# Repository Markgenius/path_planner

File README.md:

# path_planner
A line following path planner using own made iic light sensor board

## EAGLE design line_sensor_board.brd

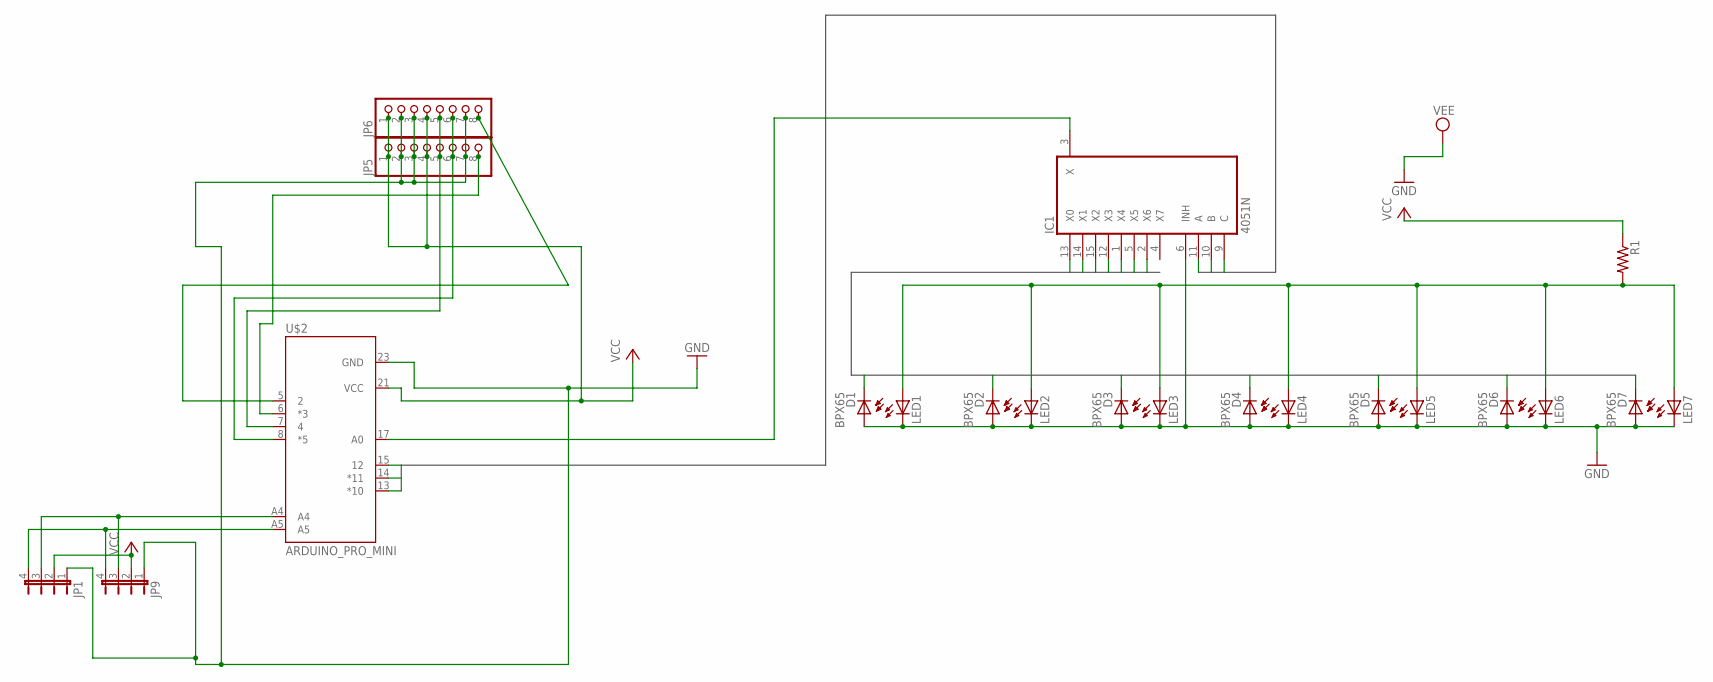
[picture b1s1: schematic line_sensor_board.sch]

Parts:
D1, D2, D3, D4, D5, D6, D7: BPX65
IC1: 4051N; DIL16
JP1, JP9: JP4E; JP4
JP5, JP6: PINHD-1X8; 1X08
LED1, LED2, LED3, LED4, LED5, LED6, LED7: LED3MM
R1: R-US_0204/5; 0204/5
U$2: ARDUINO_PRO_MINI

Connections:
A1: IC1.11 (A), U$2.15 (12)
A2: IC1.10 (B), U$2.14 (*11)
A3: IC1.9 (C), U$2.13 (*10)
B1: D7.K (C), IC1.13 (X0)
B2: D6.K (C), IC1.14 (X1)
B3: D5.K (C), IC1.15 (X2)
B4: D4.K (C), IC1.12 (X3)
B5: D3.K (C), IC1.1 (X4)
B6: D2.K (C), IC1.5 (X5)
B7: D1.K (C), IC1.2 (X6)
GND: D1.A, D2.A, D3.A, D4.A, D5.A, D6.A, D7.A, IC1.6 (INH), IC1.7 (VEE), IC1.8 (GND), JP1.1, JP5.2, JP5.3, JP5.7, JP6.2, JP6.3, JP6.7, JP9.1, LED1.K (C), LED2.K (C), LED3.K (C), LED4.K (C), LED5.K (C), LED6.K (C), LED7.K (C), U$2.23 (GND)
unnamed: IC1.3 (X), U$2.17 (A0)
unnamed: JP1.3, JP9.3, U$2.A4
unnamed: JP1.4, JP9.4, U$2.A5
unnamed: JP5.5, JP6.5, U$2.7 (4)
unnamed: JP5.6, JP6.6, U$2.8 (*5)
unnamed: JP5.8, U$2.6 (*3)
unnamed: LED1.A, LED2.A, LED3.A, LED4.A, LED5.A, LED6.A, LED7.A, R1.2
unnamed: JP6.8, U$2.5 (2)
VCC: IC1.16 (VCC), JP1.2, JP5.1, JP5.4, JP6.1, JP6.4, JP9.2, R1.1, U$2.21 (VCC)

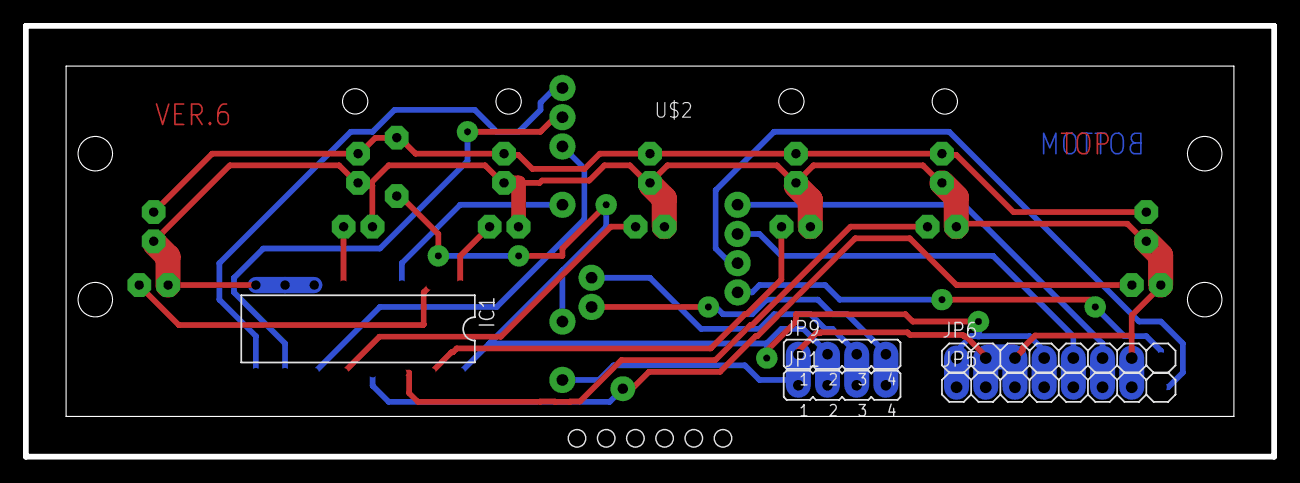
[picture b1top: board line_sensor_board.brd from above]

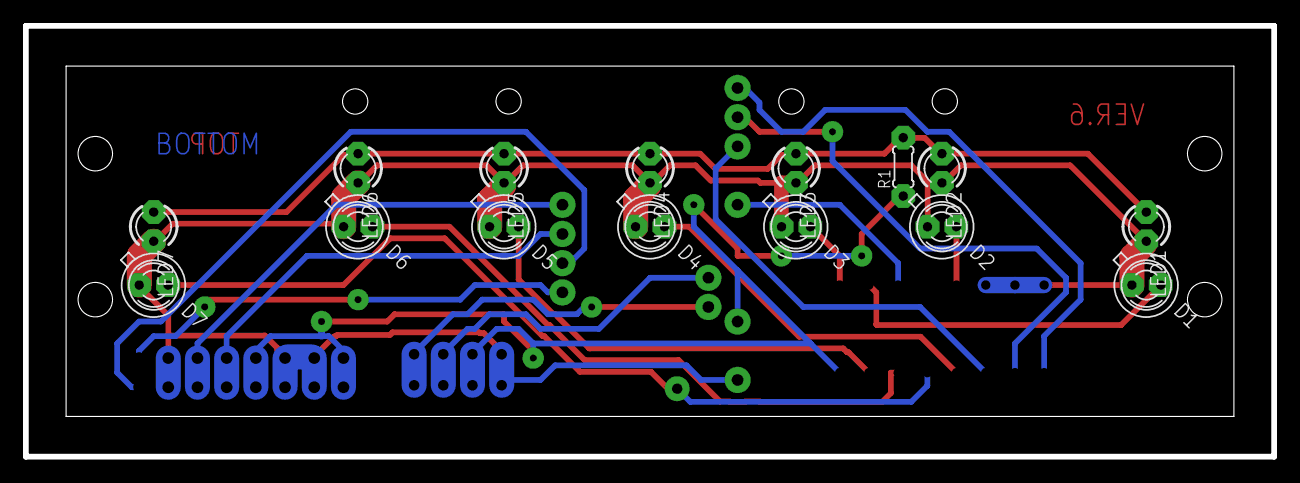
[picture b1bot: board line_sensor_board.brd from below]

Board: 2 copper layers, 108.6 x 37.5 mm, 21 parts (15 on the bottom side), 20 nets.

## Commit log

2016-04-27 Added files via upload
2016-04-27 Rename front_sensor_board/front_sensor_board.ino to firmware/light_sensor_board/front_sensor_board.ino
2016-04-27 Rename line_sensor_board.brd to hardware/line_sensor_board.brd
2016-04-27 change file locate
2016-04-29 Revert "Rename front_sensor_board/front_sensor_board.ino to firmware/light_sensor_board/front_sensor_board.ino"
    This reverts commit 13c39e732b1ad60ea9dfea0e90289d36b9fde289.
2016-04-29 Revert "Revert "Rename front_sensor_board/front_sensor_board.ino to firmware/light_sensor_board/front_sensor_board.ino""
    This reverts commit 055197a6bed5189a8a3524e3fced2bb935ddeae0.
2016-04-29 the sensor_board_program
    the program is striked out the left_color_sensor part and added 7 color
    genres but i don't know whether it can be compatible with master.Anyhow,
    it can read the data now.
2016-05-01 path_planner_program
    the slave is maybe okey but the "control_motor" function of master is
    wrong.I think i make some errors in "input" in function
    "analyse_motor_position"
2016-05-07 change the file version from rhino 5 to rhino 4
2016-05-07 line following car base
    version of Rhino 4.0
2016-06-26 a lot of things are changed
    forgot to update the program to Github from google drive. And there are
    a mountains of things have changed in these programs.

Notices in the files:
parts and their libraries:
SparkFun-Boards: Licensing: Creative Commons ShareAlike 4.0 International - https://creativecommons.org/licenses/by-sa/4.0
